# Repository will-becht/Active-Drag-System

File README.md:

# Active Drag System

## Table of Contents
- [Introduction](#introduction)
- [Flight Software](#flight-software)
- [PCB Design](#pcb-design)
- [OpenRocket](#openrocket)
- [CAD](#cad)
- [Installation](#installation)

## Introduction
This project is focused on the development of an active drag system, or air brake, for a model rocket competing in the NASA Student Launch competition (https://www.nasa.gov/learning-resources/nasa-student-launch/). This work was done on a non-competition vehicle as its advancements are intended to be used in future years' competitions.
This project demonstrates the designs of the various components, including the flight software, printed circuit board (PCB), OpenRocket analysis for the vehicle, and CAD drawings for the system. 
Due to time constraints and a focus on the main competition vehicle, the non-competition vehicle was never flown with an active drag system installed.

## Flight Software
### Overview
The `Arduino Codes` directory contains the code necessary for controlling the vehicle's Active Drag System. This system adjusts the vehicle's drag tabs based on readings from an altimeter and accelerometer to control the vehicle's apogee. The system is controlled before launch using a Bluetooth module that can connect to a user's phone, allowing for the constant monitoring of flight readiness once the system is installed in the vehicle. Data is redundantly saved to an onboard flash memory chip and SD for storage and post-flight analysis.

### Block Diagram

### Description
The flight software implements a state machine to manage the deployment of drag tabs in the Active Drag System. This system actively modulates the drag during flight to achieve a desired apogee by processing real-time data from the altimeter and accelerometer. The state machine ensures that the drag tabs are deployed or retracted based on the vehicle's altitude and acceleration, thus controlling the peak altitude accurately.

## PCB Design
### Overview
The `PCB Design` directory contains all the files related to the design and manufacturing of the vehicle's printed circuit boards (PCBs). These PCBs are used to integrate the electronic components necessary for the vehicle's operation.

### Images

### Description
PCB design is crucial for ensuring that the electronic components are connected properly. The files in this directory include design files, Gerber files for manufacturing, libraries for making the schematics, and images showing different layers and the schematic of the PCB. 

## OpenRocket
### Overview
The `OpenRocket` directory contains simulation files for the vehicle. These files can be used to simulate the vehicle's flight characteristics and performance.

### Images

### Description
OpenRocket is a model rocket simulator that allows you to design and simulate the performance of rockets. The model in this directory represents the vehicle design as well as detailed simulations that help in predicting the flight path, stability, and performance of the vehicle.

## CAD
### Overview
The `CAD` directory contains the design files for the system's structural components. This model was created in SolidWorks, and the files can be used to fabricate the parts using 3D printing.

### Images

### Description
FEA (finite element analysis) and CFD (computational fluid dynamics) were performed on the system to evaluate both its structural integrity and effectiveness as a braking system.

## Installation
To install the software and code for this project, follow these steps:

1. Clone the repository:
   ```bash
   git clone https://github.com/will-becht/Active-Drag-System

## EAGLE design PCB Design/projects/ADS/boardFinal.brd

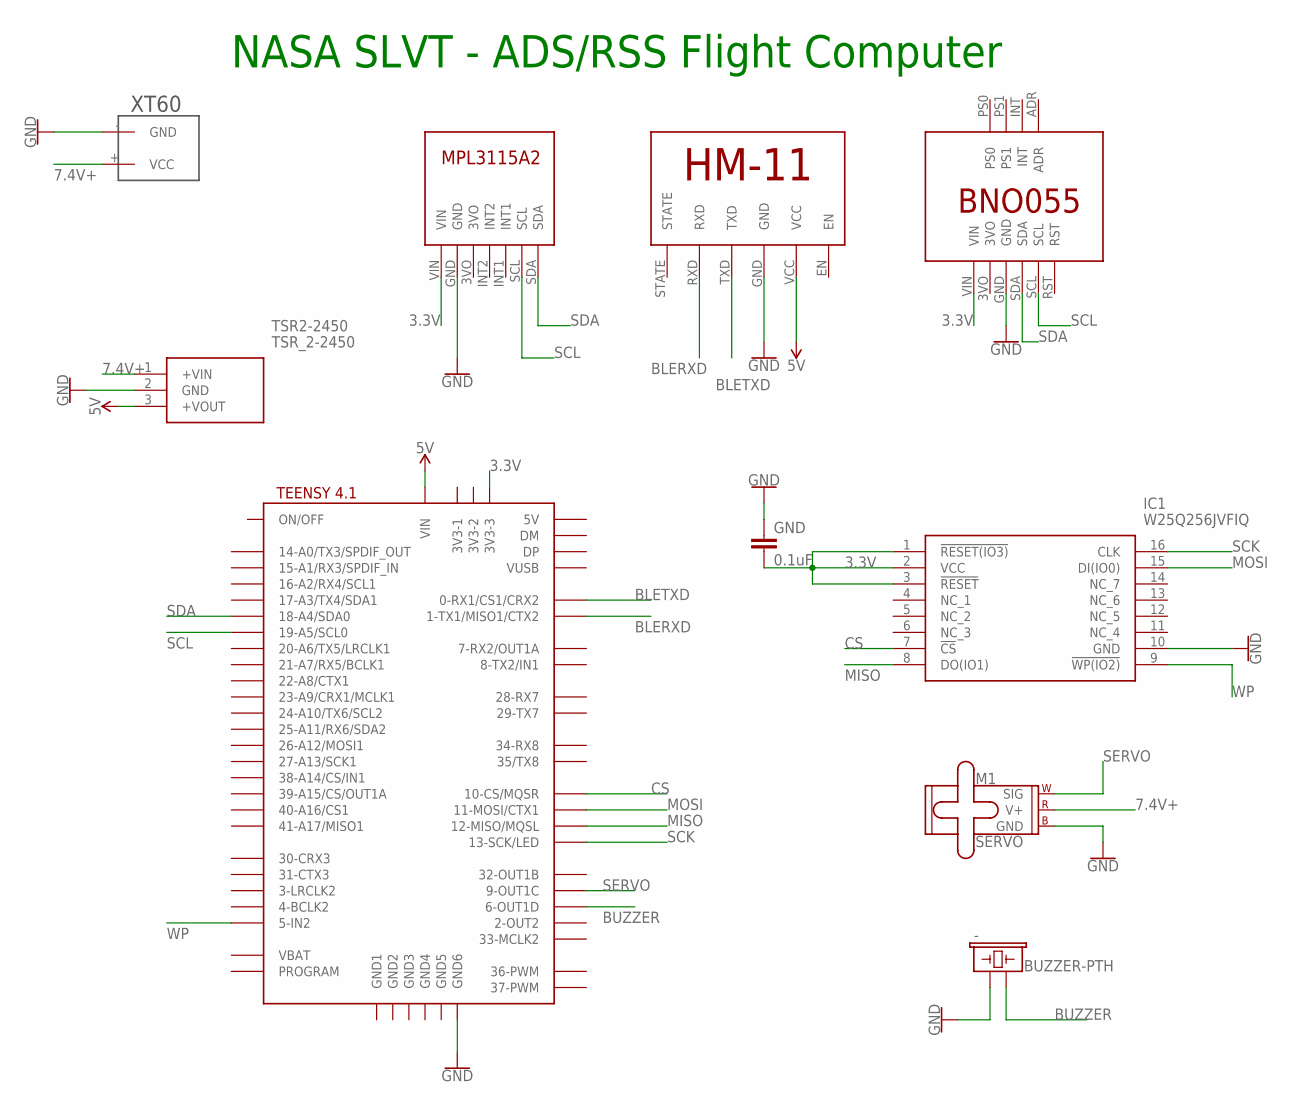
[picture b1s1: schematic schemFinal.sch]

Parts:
-: BUZZER-PTH; BUZZER-12MM
GND: 0.1uF; CAP-PTH-2.54
IC1: W25Q256JVFIQ; SOIC127P1032X264-16N
M1: SERVO; 1X03
TSR2-2450: TSR_2-2450; TSR-2
U$1: BNO055
U$2: MPL3115A2
U$3: TEENSY41-E; TENNSY41-E
U$4: HM-11
U$5: XT60

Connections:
3.3V: GND.2, IC1.1 (!RESET(IO3)), IC1.2 (VCC), IC1.3 (!RESET), U$1.VIN, U$2.VIN, U$3.3V3-3
5V: TSR2-2450.3 (+VOUT), U$3.VIN, U$4.VCC
7.4V+: M1.2 (V+), TSR2-2450.1 (+VIN), U$5.+ (VCC)
BLERXD: U$3.1-TX1/MISO1/CTX2, U$4.RXD
BLETXD: U$3.0-RX1/CS1/CRX2, U$4.TXD
BUZZER: -.- (2), U$3.6-OUT1D
CS: IC1.7 (!CS), U$3.10-CS\MQSR (10-CS/MQSR)
GND: -.+ (1), GND.1, IC1.10 (GND), M1.3 (GND), TSR2-2450.2 (GND), U$1.GND, U$2.GND, U$3.GND6, U$4.GND, U$5.- (GND)
MISO: IC1.8 (DO(IO1)), U$3.12-MISO/MQSL
MOSI: IC1.15 (DI(IO0)), U$3.11-MOSI/CTX1
SCK: IC1.16 (CLK), U$3.13-SCK/LED
SCL: U$1.SCL, U$2.SCL, U$3.19-A5/SCL0
SDA: U$1.SDA, U$2.SDA, U$3.18-A4/SDA0
SERVO: M1.1 (SIG), U$3.9-OUT1C
WP: IC1.9 (!WP(IO2)), U$3.5-IN2

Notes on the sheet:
NASA SLVT - ADS/RSS Flight Computer

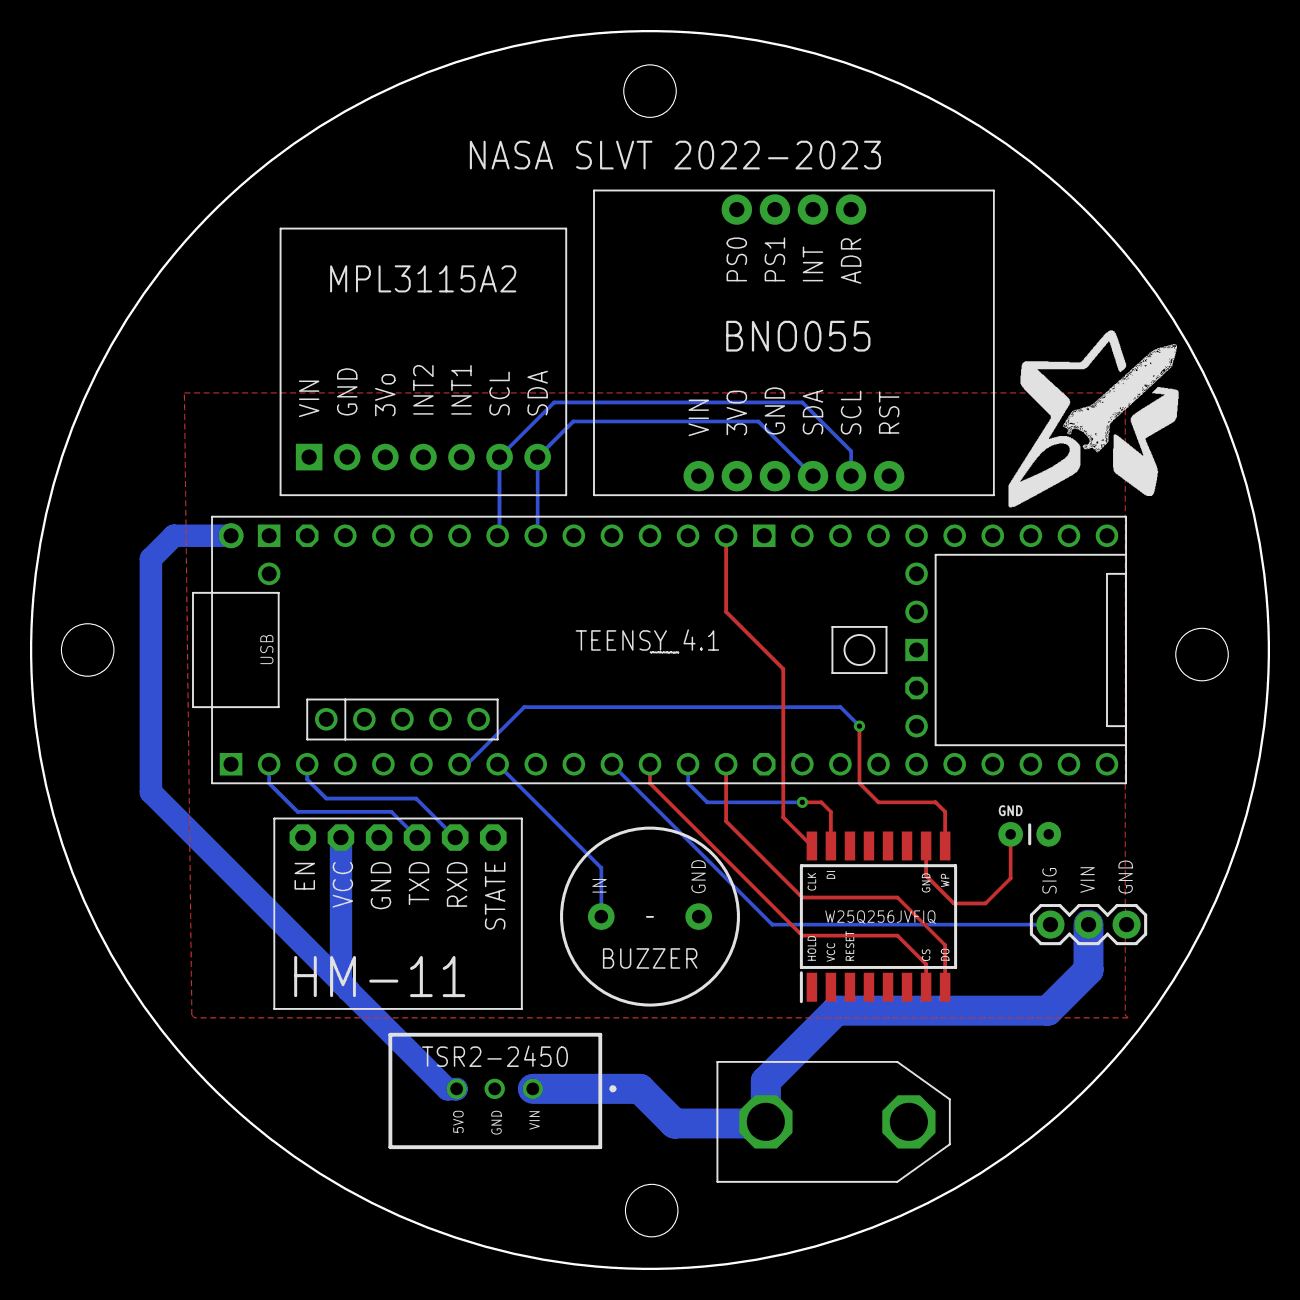
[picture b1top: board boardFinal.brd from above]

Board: 2 copper layers, 82.5 x 82.5 mm, 10 parts (0 on the bottom side), 15 nets.

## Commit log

2024-06-08 Adding flight code
2024-06-08 Adding CAD images
2024-06-08 Adding openRocket model
2024-06-08 Adding PCB files
2024-06-08 Revising image filenames
2024-06-08 Updating ReadMe
2024-06-08 Adding block diagram

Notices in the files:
parts and their libraries:
SparkFun-Capacitors: Licensing: Creative Commons ShareAlike 4.0 International - https://creativecommons.org/licenses/by-sa/4.0
